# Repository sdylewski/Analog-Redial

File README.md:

# firmware branch

Generated by `firmware/release/release.py`: the images and `latest.json` that a board's web page reads for "Check for updates". Force-pushed on every release; it only ever holds the current one. Don't edit by hand.

Current release: **v1.3.8** (2026-11-25).

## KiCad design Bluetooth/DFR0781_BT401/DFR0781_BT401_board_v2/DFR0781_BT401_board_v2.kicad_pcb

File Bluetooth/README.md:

# Bluetooth modules for the J2 header

What has been tried for the hands-free "rotary phone as a cell-phone handset" option. Newest information first.

| Module | Price | Status |
|---|---|---|
| **DFRobot DFR0781** (BT401 module, `DFR0781_BT401/`) | about $3.50 | **Preferred, and working** (hand-wired to a v5 board 2026-10-27, then on the adapter board): pairing, music, ringing, dial-out and call audio, with little call delay. Text command set with call control (answer, hang up, reject, dial, caller number); no EEPROM setup step. Adapter board `DFR0781_BT401/DFR0781_BT401_board_v1/` plugs into J2 like the BM64 carrier (built, 2026-11-19; Gerbers via KiCad's JLCPCB/PCBWay export); a v2 is in `DFR0781_BT401_board_v2/`. Build guide: [`docs/bt401.md`](../docs/bt401.md). Pin table in `DFR0781_BT401/BT401_NOTES.md`, firmware and bench log in `../archive/hardware/bt401.md`. |
| **Microchip BM64** (carrier board in `BM64/`) | about $14 | **Works and is supported**, the older alternative. UART link, pairing mode and the audio EEPROM setup verified (2026-10-20). Supply 3.2-4.2 V on `BAT_IN`, so it needs the LDO. Costs more and needs a one-time EEPROM setup that the BT401 doesn't. |
| Microchip BM83 | about $12.20 | Candidate only. Digikey lists BM83SM1-00AA, -00AB and -00TA (read the Microchip ordering table before buying). Same 0xAA binary framing as the BM64 per Microchip's UART command documentation, so the driver would probably adapt, but footprint and pinout are not confirmed to match; needs its own carrier. Not worth the $1.80 saving unless the BM64 becomes hard to get. |
| **BK3266 / "BH519"** (`BK3266_do_not_use/`, `BK3266_board_v1` KiCad project) | about $3 | **Not working as intended.** The module powers on and pairs with a phone as an audio device ("BH519"), but its UART never answers (binary or text, 1200-460800 baud, TX/RX both ways), so the firmware cannot control calls. Notes and bench log: `BK3266_do_not_use/BK3266_RESEARCH.md` and `../archive/hardware/bk3266.md`. Kept for reference only; its firmware driver was removed (last in `v1.0.1`). |

Firmware lives in `firmware/components/bt_companion/` (the BM64 and BT401 drivers). The public docs lead with the BT401 ([`docs/bt401.md`](../docs/bt401.md), [`docs/bom.md`](../docs/bom.md#bluetooth-board-v5-and-v6-expansion-header-optional)) and describe the BM64 as the alternative.

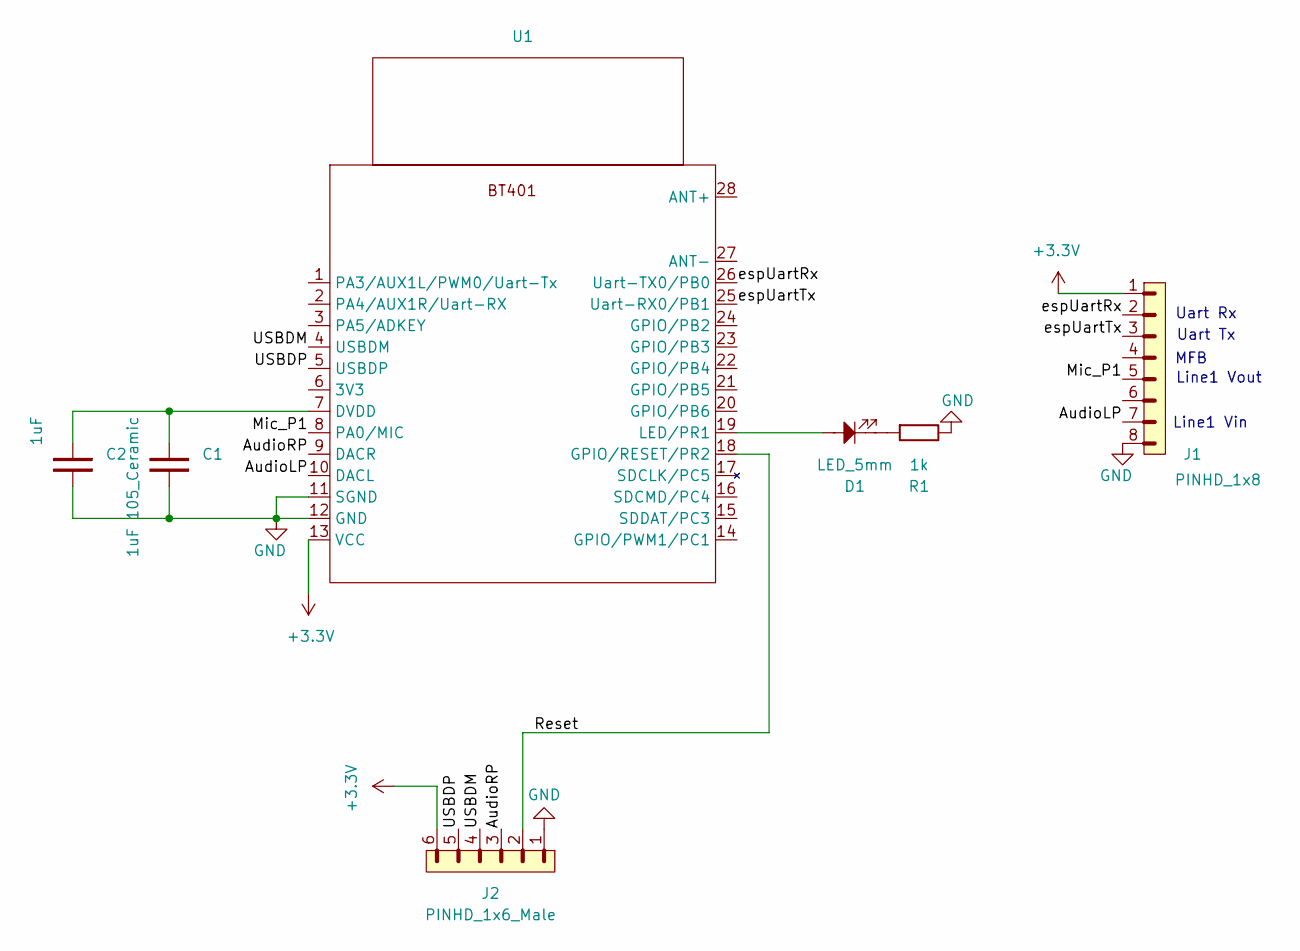
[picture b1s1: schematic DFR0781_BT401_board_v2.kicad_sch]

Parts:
C1: 1uF 105_Ceramic; C_Disc_D5.0mm_W2.5mm_P5.00mm
C2: 1uF; C_0402_1005Metric
D1: LED_5mm; LED_D5.0mm
J1: PINHD_1x8; PinHeader_1x08_P2.54mm_Vertical
J2: PINHD_1x6_Male; PinHeader_1x06_P2.54mm_Vertical
R1: 1k; R_Axial_DIN0207_L6.3mm_D2.5mm_P10.16mm_Horizontal
U1: DFR0781_BT401_new

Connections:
+3.3V: J1.1, J2.6, U1.13 (VCC)
/AudioLP: J1.7, U1.10 (DACL)
/AudioRP: J2.3, U1.9 (DACR)
/Mic_P1: J1.5, U1.8 (PA0/MIC)
/Reset: J2.2, U1.18 (GPIO/RESET/PR2)
/USBDM: J2.4, U1.4 (USBDM)
/USBDP: J2.5, U1.5 (USBDP)
/espUartRx: J1.2, U1.26 (Uart-TX0/PB0)
/espUartTx: J1.3, U1.25 (Uart-RX0/PB1)
GND: C1.2, C2.2, J1.8, J2.1, R1.2, U1.11 (SGND), U1.12 (GND)
unnamed: D1.1, R1.1
unnamed: C1.1, C2.1, U1.7 (DVDD)
unnamed: D1.2, U1.19 (LED/PR1)

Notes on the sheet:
Uart Tx
Line1 Vin
Uart Rx
Line1 Vout
MFB

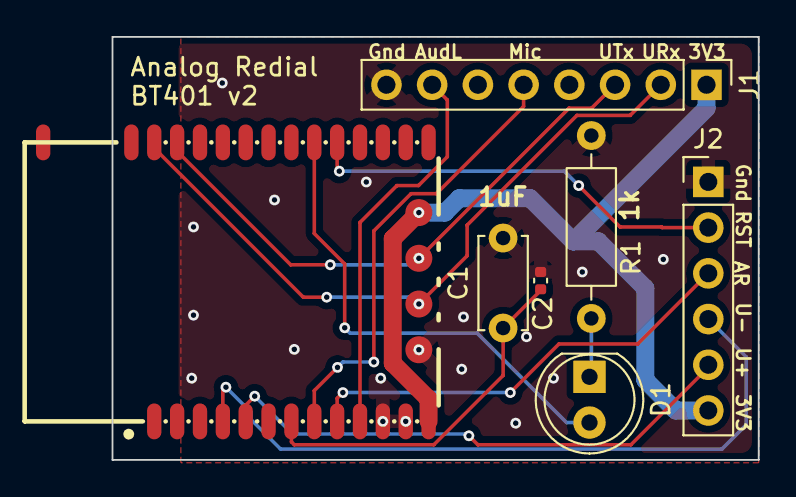
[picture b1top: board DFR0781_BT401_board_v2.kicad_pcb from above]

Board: 2 copper layers, 35.9 x 23.5 mm, 7 parts (0 on the bottom side), 13 nets.

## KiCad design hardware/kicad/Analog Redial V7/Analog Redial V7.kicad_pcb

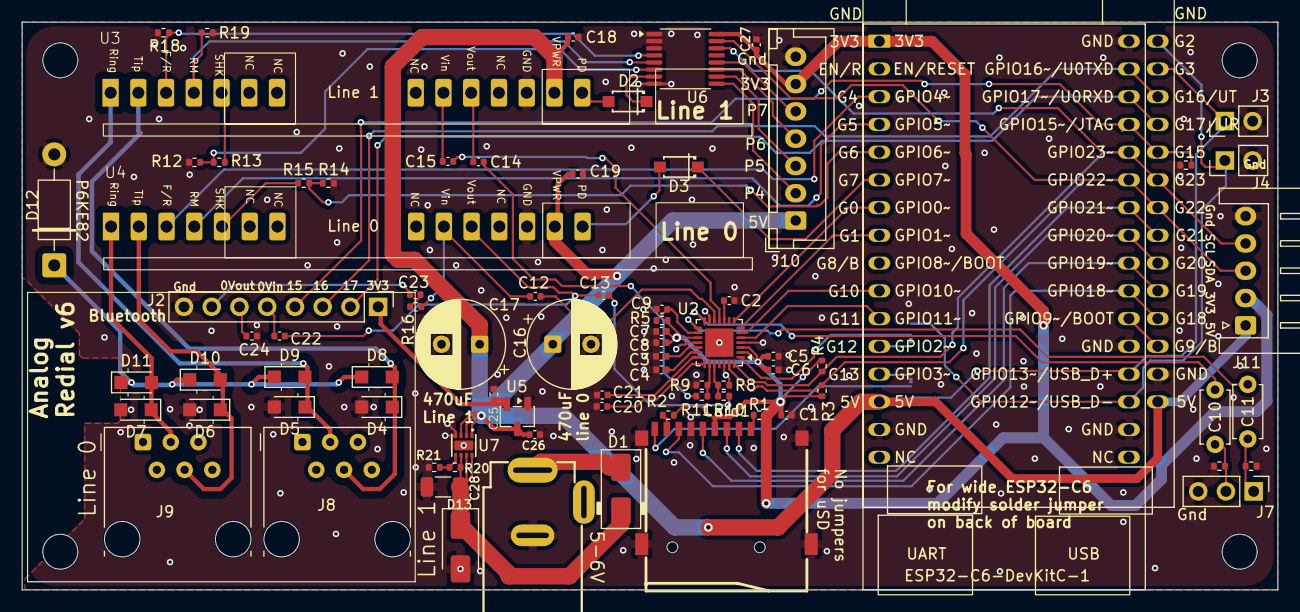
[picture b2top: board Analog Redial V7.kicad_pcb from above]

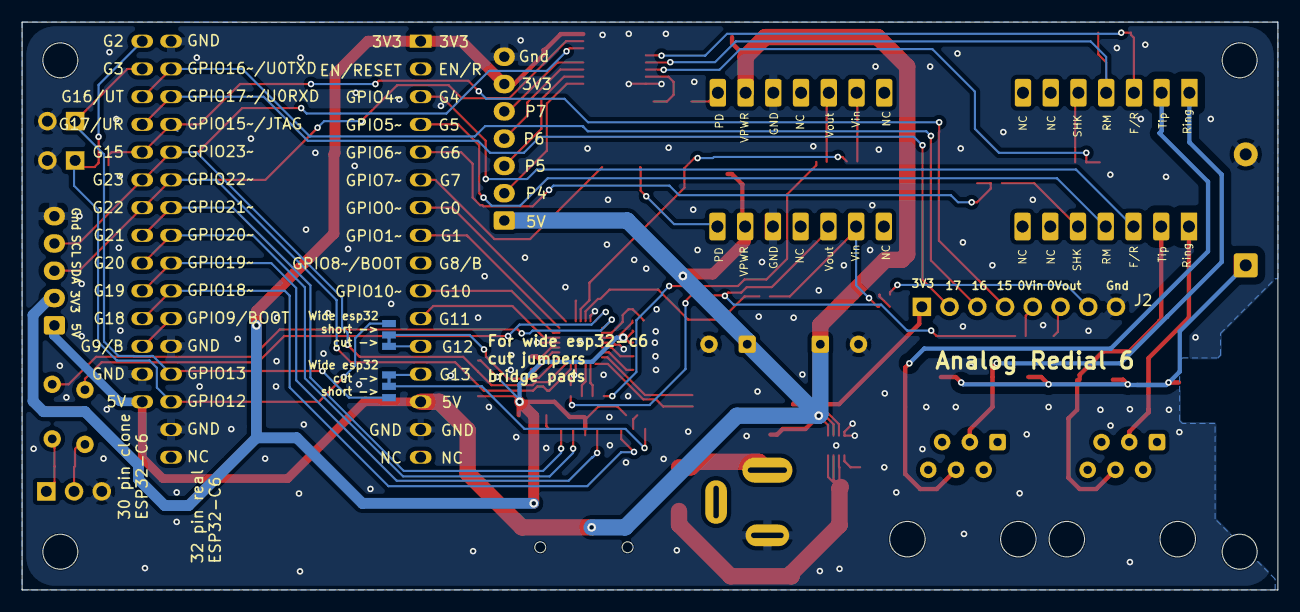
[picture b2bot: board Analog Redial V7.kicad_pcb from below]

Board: 2 copper layers, 115.0 x 52.0 mm, 85 parts (2 on the bottom side), 73 nets.

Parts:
C1, C5, C6, C8, C9, C13, C14, C18, C19, C20, C21, C27: 100nF; C_0402_1005Metric
C2, C3, C4, C22, C23, C24, C25, C26: 1uF; C_0402_1005Metric
C7: 10uF; C_0402_1005Metric
C10, C11: 47uF; C_Disc_D4.7mm_W2.5mm_P5.00mm
C12, C15: 10nF; C_0402_1005Metric
C16, C17: 470uF 16V; CP_Radial_D8.0mm_P3.50mm
C28: 1uF 50V; C_1206_3216Metric
Card1: TF-01A
D1: SS34; D_SMA
D2, D3: 1N4148; 1N4148W_C81598
D4, D5, D6, D7, D8, D9, D10, D11: SM4007PL; Nexperia_CFP3_SOD-123W
D12: D_Zener P6KE82; D_DO-41_SOD81_P10.16mm_Horizontal
D13: SMAJ22A; D_SMA
H1, H2, H3, H4: MountingHole_M3; MountingHole_3.2mm_M3
J1: Barrel_Jack_PTH_Slot; Barrel_Jack_PTH_Slot_tight
J2: PINHD_1x8_Male; PinHeader_1x08_P2.54mm_Vertical
J3, J4: PINHD_1x2_Male; PinHeader_1x02_P2.54mm_Vertical
J7: PINHD_1x3_Male; PinHeader_1x03_P2.54mm_Vertical
J8, J9: RJ12; RJ12_Amphenol_87180_Horizontal
J10: GPIO Expansion; JST_XH_B7B-XH-A_1x07_P2.50mm_Vertical
J11: Accessory; JST_XH_S5B-XH-A_1x05_P2.50mm_Horizontal
JP2, JP3: Jumper_3_NC-1_Trace_NoSilk
R1, R2, R8, R9, R10, R11, R13, R15, R18, R19, R21: 10k; R_0402_1005Metric
R3, R4: 4.7k; R_0402_1005Metric
R5: 10R; R_0402_1005Metric
R6, R7: 47k; R_0402_1005Metric
R12, R14, R17: 100k; R_0402_1005Metric
R16: 1k; R_0402_1005Metric
R20: 39k; R_0402_1005Metric
U1: ESP32-C6-DevKitC-1; ESP32-C6-DevKitC-dual
U2: ES8388; QFN-28-1EP_4x4mm_P0.45mm_EP2.6x2.6mm
U3, U4: AG1171; AG1171_SIL
U5: XC6206P332MR; SOT-23-3
U6: TCA9534APWR; TSSOP-16_4.4x5mm_P0.65mm
U7: WS3222D-8/TR; WS3222D_WDFN-8_2x2mm_P0.5mm

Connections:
+3.3V: C1.1, C5.2, C6.2, C7.2, C8.2, C27.1, Card1.4 (VDD), J10.6, J11.2, R1.2, R2.1, R3.1, R4.1, R5.1, U1.1 (3V3), U2.2 (DVDD), U2.3 (PVDD), U2.17 (AVDD), U6.16 (VDD)
+3.6V_BM: C25.1, J2.1, U5.2 (VO)
+5V: C16.1, C17.1, C18.1, C19.1, C26.1, J10.1, J11.1, U1.14 (5V), U3.13 (Vpwr), U4.13 (Vpwr), U5.3 (VI), U7.1 (OUT), U7.2 (OUT), U7.3 (OUT)
/CH0_Mic: C13.1, R10.1
/CH0_Spk: C12.1, U2.12 (LOUT1)
/CH1_Mic: C14.2, R11.1
/CH1_Spk: C15.2, U2.11 (ROUT1)
/EXP_P4: J10.2, U6.9 (P4)
/EXP_P5: J10.3, U6.10 (P5)
/EXP_P6: J10.4, U6.11 (P6)
/EXP_P7: J10.5, U6.12 (P7)
/GPIO12: J4.1, JP3.3 (B), U1.19 (GPIO12/USB_D-)
/GPIO13: J3.1, JP2.3 (B), U1.20 (GPIO13/USB_D+)
/I2C_SCL: J11.4, R4.2, U1.28 (GPIO23), U2.28 (CCLK), U6.14 (SCL)
/I2C_SDA: J11.3, R3.2, U1.27 (GPIO22), U2.27 (CDATA), U6.15 (SDA)
/I2S_BCLK: U1.11 (GPIO11), U2.5 (SCLK)
/I2S_DIN: U1.7 (GPIO0), U2.8 (ASDOUT)
/I2S_DOUT: U1.10 (GPIO10), U2.6 (DSDIN)
/I2S_LRCK: U1.8 (GPIO1), U2.7 (LRCK)
/I2S_MCLK: JP3.2 (C), U2.1 (MCLK)
/Line0Vin: C12.2, R16.1, U4.9 (Vin)
/Line0Vout: C13.2, C22.1, U4.10 (Vout)
/Line0_F/R: U1.3 (GPIO4/MTMS), U4.3 (F/R)
/Line0_PD: D3.1 (K), U1.6 (GPIO7)
/Line0_RM: U1.4 (GPIO5/MTDI), U4.4 (RM)
/Line0_SHK: R14.2, R15.1, U1.5 (GPIO6)
/Line1Ring: D7.1 (K), D11.2 (A), J9.3, U4.1 (Ring)
/Line1Tip: D6.1 (K), D10.2 (A), J9.4, U4.2 (Tip)
/Line1_F/R: R18.2, U3.3 (F/R), U6.4 (P0)
/Line1_PD: D2.1 (K), U6.7 (P3)
/Line1_RM: R19.2, U3.4 (RM), U6.5 (P1)
/Line1_SHK: R12.2, R13.1, U6.6 (P2)
/Line2Ring: D5.1 (K), D9.2 (A), J8.3, U3.1 (Ring)
/Line2Tip: D4.1 (K), D8.2 (A), J8.4, U3.2 (Tip)
/MFB: J2.4, R17.2, U1.29 (GPIO15/JTAG)
/P6K: D8.1 (K), D9.1 (K), D10.1 (K), D11.1 (K), D12.1 (K)
/SD_CD: Card1.9 (CD), JP2.2 (C)
/SD_CLK: Card1.5 (CLK(SCLK)), U1.24 (GPIO19)
/SD_CS: Card1.2 (CDDAT3(CS)), U1.26 (GPIO21)
/SD_MISO: Card1.7 (DAT0(D0)), U1.23 (GPIO18)
/SD_MOSI: Card1.3 (CMD(DI)), U1.25 (GPIO20)
/VDC_IN: C28.1, D1.1 (K), D13.1 (K), R20.1, U7.6 (IN), U7.7 (IN), U7.8 (IN)
GND: C1.2, C2.1, C3.1, C4.1, C5.1, C6.1, C7.1, C8.1, C9.1, C16.2, C17.2, C18.2, C19.2, C20.1, C21.1, C24.1, C25.2, C26.2, C27.2, C28.2, Card1.6 (VSS), Card1.10 (GND), Card1.11 (GND), Card1.12 (GND), Card1.13 (GND), D4.2 (A), D5.2 (A), D6.2 (A), D7.2 (A), D12.2 (A), D13.2 (A), J1.GND, J2.8, J3.2, J4.2, J7.3, J10.7, J11.5, R6.1, R7.2, R8.1, R9.1, R12.1, R14.1, R17.1, R18.1, R19.1, R21.2, U1.15 (GND), U1.18 (GND), U1.21 (GND), U1.32 (GND), U2.4 (DGND), U2.13 (HPGND), U2.18 (AGND), U2.26 (CE), U2.29 (EPAD), U3.12 (GND), U4.12 (GND), U5.1 (GND), U6.1 (A0), U6.2 (A1), U6.3 (A2), U6.8 (GND), U7.4 (GND), U7.9 (GND)
unnamed: C10.1, J7.2, R6.2
unnamed: C11.1, J7.1, R7.1
unnamed: C22.2, J2.5
unnamed: C23.1, R16.2
unnamed: C23.2, J2.7
unnamed: C24.2, J2.6
unnamed: Card1.8 (DAT1(RSV)), R2.2
unnamed: Card1.1 (DAT2(RSV)), R1.1
unnamed: D1.2 (A), J1.PWR
unnamed: D2.2 (A), U3.14 (PD)
unnamed: D3.2 (A), U4.14 (PD)
unnamed: JP2.1 (A), U1.13 (GPIO3)
unnamed: JP3.1 (A), U1.12 (GPIO2)
unnamed: J2.3, U1.31 (GPIO16/U0TXD)
unnamed: J2.2, U1.30 (GPIO17/U0RXD)
unnamed: C3.2, U2.19 (ADCVREF)
unnamed: C9.2, R5.2, U2.16 (HPVDD)
unnamed: R8.2, R10.2, U2.24 (LIN1)
unnamed: C20.2, U2.22 (LIN2)
unnamed: C11.2, U2.15 (LOUT2)
unnamed: R9.2, R11.2, U2.23 (RIN1)
unnamed: C21.2, U2.21 (RIN2)
unnamed: C10.2, U2.14 (ROUT2)
unnamed: C4.2, U2.20 (VMID)
unnamed: C2.2, U2.10 (VREF)
unnamed: R13.2, U3.5 (SHK)
unnamed: C15.1, U3.9 (Vin)
unnamed: C14.1, U3.10 (Vout)
unnamed: R15.2, U4.5 (SHK)
unnamed: R20.2, R21.1, U7.5 (OVLO)

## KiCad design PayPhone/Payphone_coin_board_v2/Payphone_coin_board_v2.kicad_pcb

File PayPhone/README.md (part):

# Payphone with Analog Redial

**Working on one payphone.** One coin board v1 is built, on a v6 main board, and runs the
project's first phone, a GTE / Quadrum 120B style set: coins are counted from its coin
switches, a message plays for each, and the coins are collected or returned by its coin relay
(2026-11-14 and 15). No other phone has been tried. Coin board v2 (an on-board 3.3 V regulator
and a ground-start relay on P7) is being drawn in `Payphone_coin_board_v2/`.

> ⚠️ **The coin board makes up to 119 V DC and stores it in a capacitor: it can injure or
> kill.** Read [Safety first](../docs/hardware-coin-board.md#safety-first-high-voltage) before
> you build or power one. It is provided as is.

Analog Redial can run a real coin payphone: the handset lifts, a spoken message asks for
coins, the coin switches (or the line's coin tones) add up the credit, and the board
collects or returns the coins by firing the phone's coin relay.

| Doc | Covers |
|---|---|
| This one | the project as a whole: what the pieces are, status, payphone types, links |
| [docs/coin-board.md](docs/coin-board.md) | the coin board: how it works, output stage wiring pin by pin, parts and PCB layout |
| [docs/payphone-firmware.md](docs/payphone-firmware.md) | the firmware: the Payphone tab (coin tones, coin required, messages, log) and the coin board's driver |

Public version of the board reference: [docs/hardware-coin-board.md](../docs/hardware-coin-board.md).

## The pieces

- **Main board:** any Analog Redial board for the Payphone tab (coin required, messages,
  coin tones, the coin counter). The coin board plugs into v6's J11 I²C header.
- **Coin board** (`Payphone_coin_board_v1/`): makes up to 119 V to fire the coin relay in
  either direction, reads the 5 / 10 / 25 cent switches, and talks I²C. One built and working.
- **Instruction cards** (`instruction_cards/`): the printed cards for the phone's
  upper and lower panels, and their standard sizes (see its README).
- **Firmware** (`firmware/components/payphone/`, `coinboard/`): see
  [docs/payphone-firmware.md](docs/payphone-firmware.md).

*Coin board v1 mounted in the phone on a 3D-printed bracket (`Payphone_coin_board_v2/Coin board bracket/`).*

*Coin board v1 mounted in the phone on a 3D-printed bracket (`Payphone_coin_board_v2/Coin board bracket/`).*

## Payphone types

Payphones differ in how they report coins and how their coin relay is driven. The housing
says little: a Quadrum is only a case, and the same case held many different boards. What
matters is **what handles the coins**, and the Payphone tab's **Phone type** card asks for
both, in that order (`firmware/components/payphone/payphone_types.c`, see
[docs/payphone-firmware.md](docs/payphone-firmware.md#phone-type)).

**What handles the coins** (the categories the firmware uses):

| Inside | Coins seen by | Relay worked by | Analog Redial's part |
|---|---|---|---|
| **Coin switches and relay wired to the coin board** (own board removed or bypassed) | the coin board | the coin board, 19-119 V | everything: credit, messages, collect and return |
| **Smart (COCOT) board, working and programmed**: Elcotel, Protel, Intellicall, Ernest, AT&T Private Payphone, Nortel Millennium | the phone's board | the phone's board | only the line; untried. Most need programming with their own software and a modem; an Elcotel 5 also needs a 6 V battery and line voltage for its escrow relay |
| **Coin-line totalizer** (the telephone companies' "dumb" phones: WE 1C, 1D, 2C, Gemini 4032C) | coin tones on the line (1700 + 2200 Hz) | on a real coin line, the exchange, with about ±130 V on the line; here, the coin board if the relay's wires are moved to J2 (untried) | credit and messages from the tones. A coin-first board also waits for a ground start (coin board v2) |
| **No coin board: used as a phone** (the phone's own coin parts left alone) | coin tones on the line, if the phone sends any (untried) | nobody: coins can't be collected or returned | dial tone, ringing and calls; optionally credit and messages from the tones |
| **Coinless** | - | - | nothing: a normal phone |

**Housings** in the menu, with the insides each is found with (usual first):

| Housing | Made | Insides |
|---|---|---|
| Quadrum / GTE 120B style (smart-phone housings; they differ in where the coin return lever is) | 1980s-2000s | coin board, no coin board, smart, coinless |
| Western Electric / AT&T single-slot (1C, 1D, 2C) | 1965-1990s | coin-line, no coin board, smart (retrofits: Protel 4000/8000, Elcotel 5501), coin board, coinless |
| Western Electric 3-slot (coins ring bells and a gong, no tones) | 1920s-1960s | coinless |
| Nortel Millennium | 1990s-2000s | smart, no coin board, coinless |
| Other, or not sure | | any; "not sure" sets nothing and shows every card |

Single-slot board names (from telesfor.org): first digit 1 wall, 2 flush, 3 electronic; letter
A coin first, C coin first or dial tone first, D dial tone first, E postpay; last digit 1 rotary,
2 Touch-Tone, 3 manual. So a 1D2 is a wall-mounted, dial-tone-first, Touch-Tone phone.

Only the coin board choice, on the first phone, has been tried. The menu labels every other
choice "untested" until a phone has been shown to work with it, and the Coin tones card carries
the same label: no real phone's coin tones have been heard yet.

The tables below are what has been **measured**, one row per phone. A measured phone is also a
`KNOWN[]` entry in `payphone_types.c`, so choosing it fills in the coin board's pulse and swap (when the entry has a swap).

To add a phone, add a row to each table (and a `KNOWN[]` entry), mark anything not measured
**[verify]**, and note in the last column where the numbers came from.

### 1. Identification

| Phone | Housing | Controller board | Made | Source |
|---|---|---|---|---|
| **GTE / Quadrum 120B style** (the project's first phone) | GTE / Quadrum, coin return lower right | **HB-1301-B** (40-pin DIP, two CP Clare reed relays, 310 V gas tube); smart or dumb not known **[verify]** | week 51, 1997 | photos and bench tests, 2026-10-24 to 2026-10-31 |

### 2. Coin detection

| Phone | Sensor | Cable | Wires | Signal | Coins | Coin tones |
|---|---|---|---|---|---|---|
| GTE / Quadrum 120B style | passive coin switches (measured) | 4-wire, Molex KK 396 (coin board J3) | green common; white quarter, red dime, blue nickel | contact to common; closes for 40-95 ms per coin (measured with the coin switch capture: nickel 44-95 ms, dime 44-51 ms, quarter about 40 ms, with up to 3 ms of chatter at first contact) | 5, 10, 25 cents | not checked **[verify]** |

### 3. Coin relay

| Phone | Relay | Coils | Wires | Resistance | Operates at | Direction | Switch-off | Cable |
|---|---|---|---|---|---|---|---|---|
| GTE / Quadrum 120B style | **HD550002C** (QTI) | one, polarized | white and green to the coil path; red not connected | about 1 k at rest; 0.1 ohm across the coil once operated | 55 V no, 60 V yes on the bench (relay alone); **in the phone it needs 87 V** (about 67 mA through the 1.1 k coil) | white positive: lever left, **collect** (bench; confirm in the phone) **[verify]**; reversed: lever right, return | a contact on the white-green path opens as it operates, so it switches itself off | 3-wire, Molex KK 396 (coin board J2) |

### 4. Coin board settings

| Phone | Relay connector | J10 (two-coil) | HV (J14, J7-J9) | Pulse | Swap | Coin 4 | Tested |
|---|---|---|---|---|---|---|---|
| GTE / Quadrum 120B style | J2 | off | fit **J14 + J7 (87 V)**; 60 V and 78 V don't give the relay enough current with the phone's levers attached | 100 ms works (the armature moves at about 65-70 ms, seen as a dip in the coil current); 100-150 ms | **off** (the default): confirmed in the phone, collect and return both go the right way. On the bench alone, white positive collected, which looked like "on" | 0 (not fitted) | **yes**: collect and return in the phone, on answer and at hang-up (2026-11-14/15, 87 V, 100 ms) |

Notes on the columns:

- **HV** is set by shunts, not by firmware: [docs/coin-board.md](docs/coin-board.md#part-1-design)
  Part 1, section 6 has the table. Without J14 it stays at about 19 V, for 12-24 V coils.
- **Pulse** and **Swap** are on the Payphone tab's coin board card. Swap reverses which
  way Collect and Return drive the relay.
- **Coin 4** is the cents value of the fourth coin input (0 = only logged).

### What the first phone taught

- **The relay latches its flap down.** After a fire the white flap stays down, and the relay
  can't fire again while it is (its own contact is open): the firmware reports "no current
  (latched down?)". The next coin entering the chute pushes it back up. A stiff coin lever that
  wouldn't return caused the stuck-down states on the bench, and sent every coin straight to
  the box: it needed taking out and oiling.
- **Bench voltage isn't phone voltage.** The relay moved at 60 V on the bench, alone; in the
  phone, with its levers attached, it needs 87 V.
- **Too many coins jam the hopper** when released together, hence the coin limit (8 by
  default) on the Payphone tab.
- **The coin return lever** ("coin release") only widens the coin path to free a jam; it
  doesn't return the hopper's coins.
- **A reversed J3 plug** counts nickels but not dimes or quarters.
- **Marginal 3.3 V on the cable** (a bad crimp, or a clone module's small regulator) gives
  odd ADC readings and resets; coin board v2 has its own regulator for this.

### Still to find out for the first phone

- Whether the HB-1301-B board is smart (counts coins itself) or dumb (central-office
  controlled), and whether the phone sends coin tones on the line. It is bypassed now, so this
  only matters for someone running the phone on its own board.

## References

- [telesfor.org payphone wiki](https://telesfor.org/payphones/doku.php?id=smart): the best single
  reference found. Smart (COCOT) payphones by maker ([Elcotel](https://telesfor.org/payphones/doku.php?id=smart:elcotel),
  [Protel](https://telesfor.org/payphones/doku.php?id=smart:protel),
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
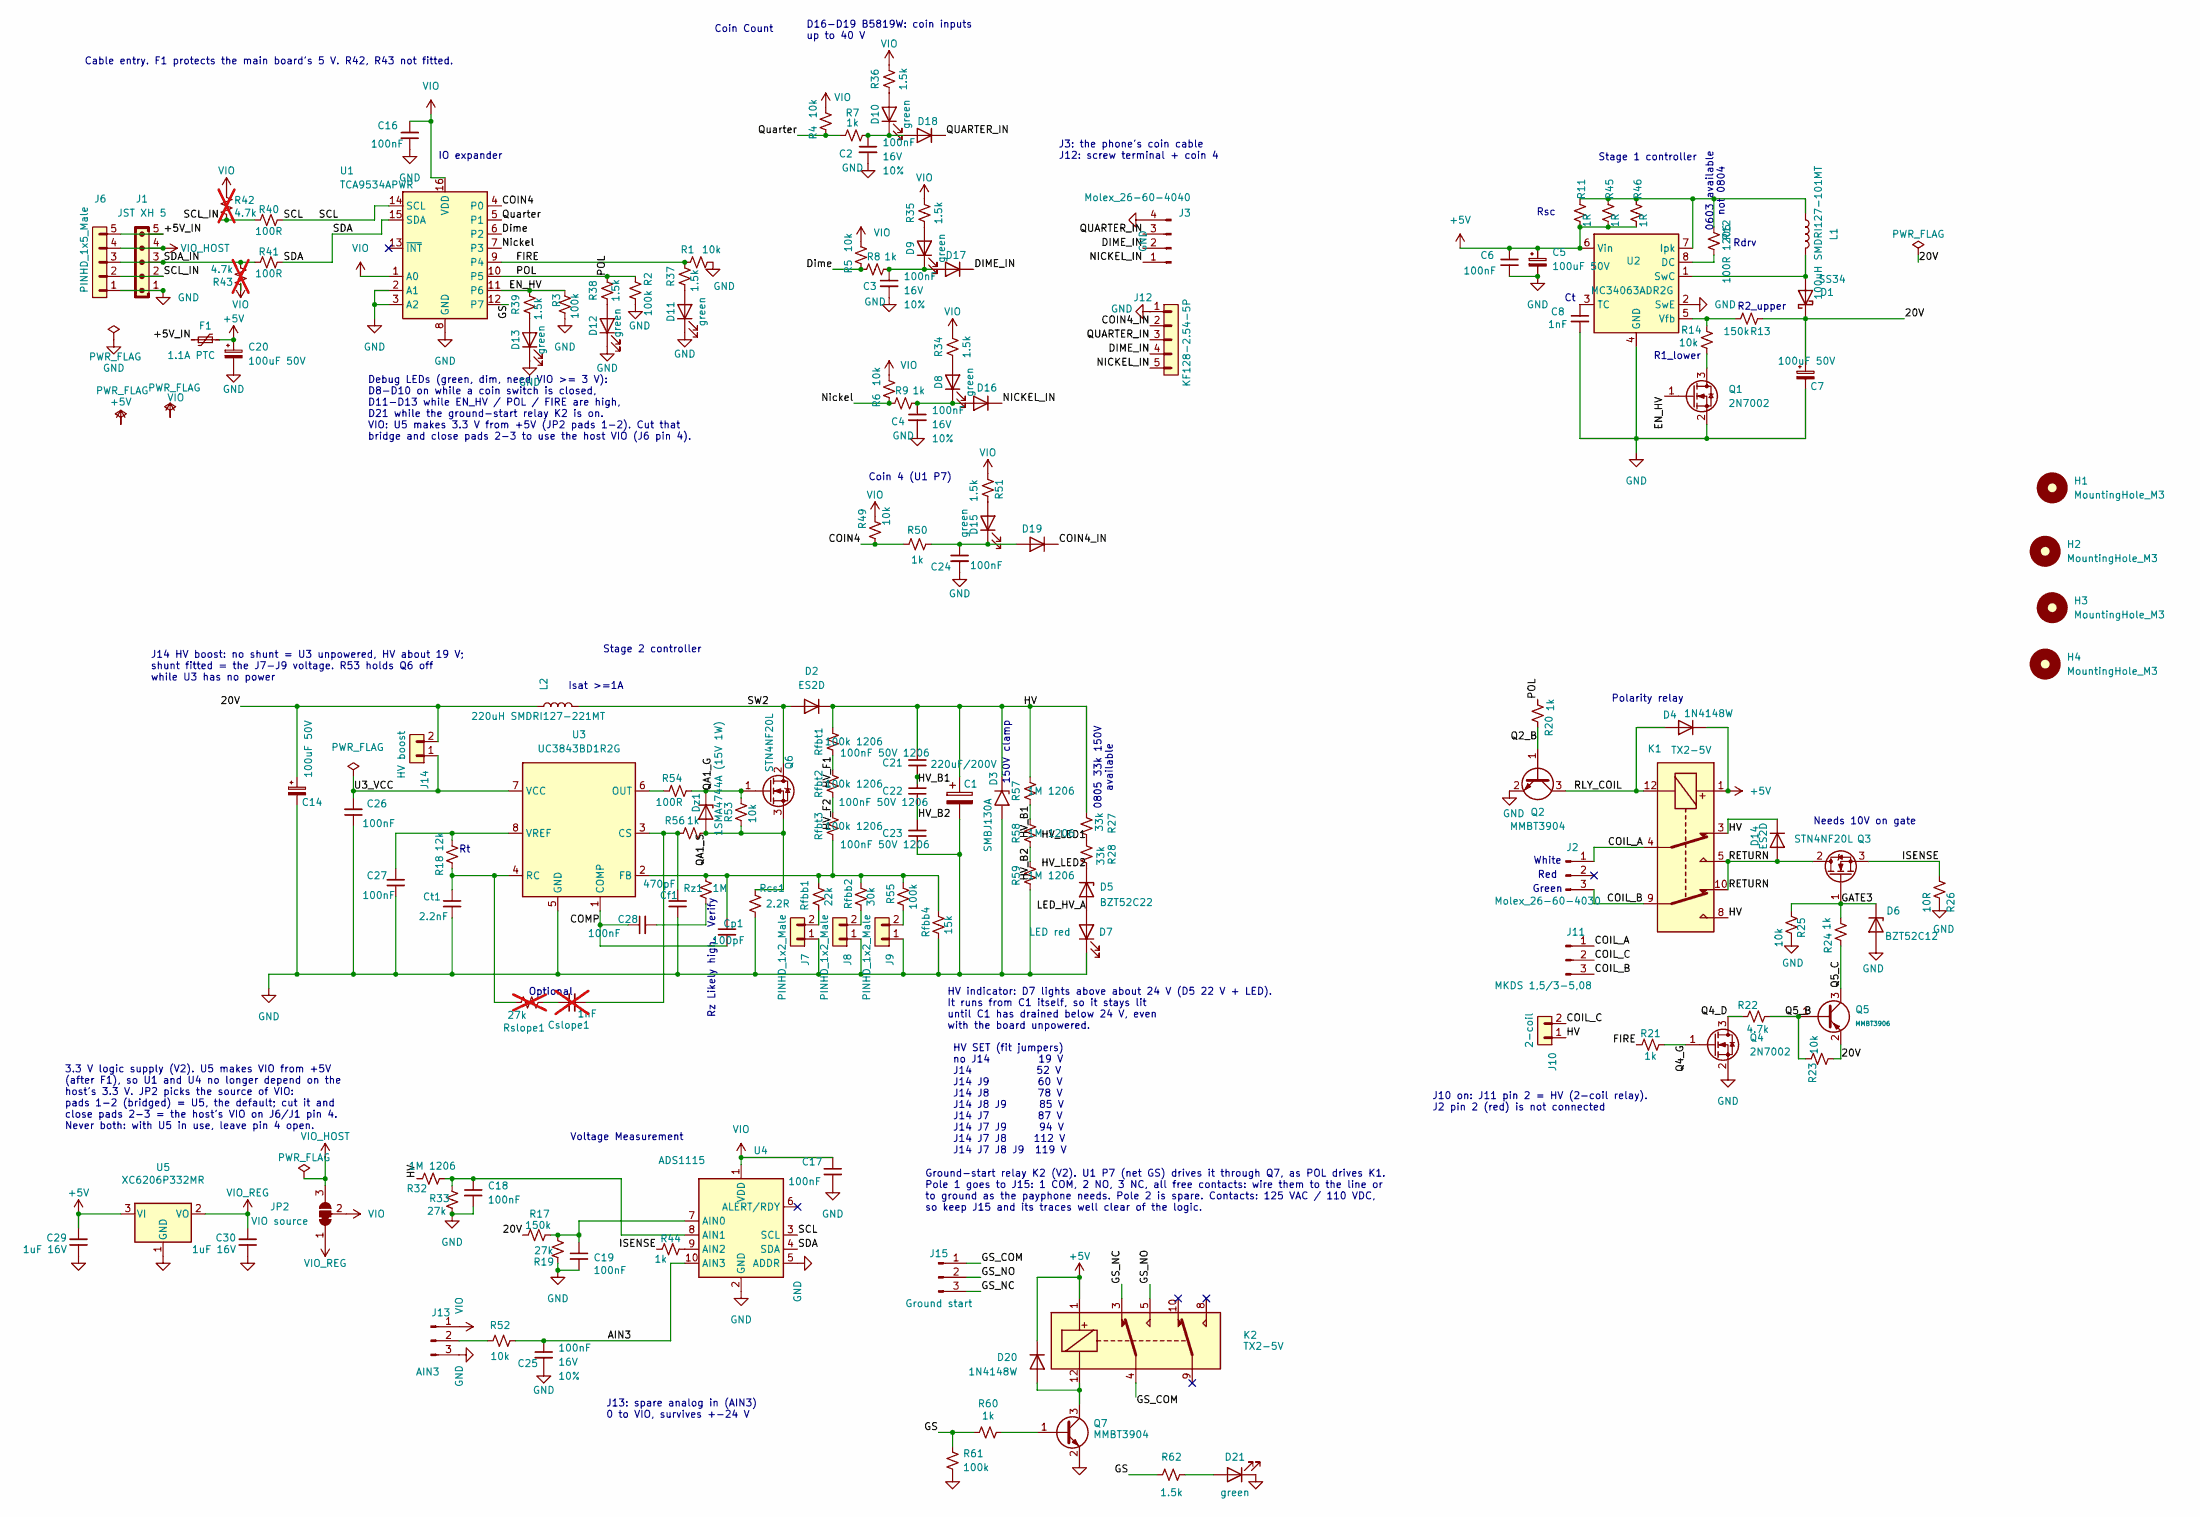
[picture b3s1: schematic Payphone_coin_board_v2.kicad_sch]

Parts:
C1: 220uF/200V; CP_Radial_D18.0mm_P7.50mm
C2, C3, C4, C24, C25: 100nF; C_0805_2012Metric; Voltage 16V; Tolerance 10%; LCSC C28233
C5, C7, C14, C20: 100uF 50V; CP_Elec_8x10
C6, C16, C17, C18, C19, C26, C27, C28: 100nF; C_0805_2012Metric; LCSC C28233
C8: 1nF; C_0805_2012Metric; LCSC C46653
C21, C22, C23: 100nF 50V 1206; C_1206_3216Metric; LCSC C24497
C29, C30: 1uF 16V; C_0805_2012Metric
Cf1: 470pF; C_0805_2012Metric; LCSC C1743
Cp1: 100pF; C_0805_2012Metric; LCSC C1790
Cslope1: 1nF; C_0805_2012Metric; LCSC C46653; not fitted
Ct1: 2.2nF; C_0805_2012Metric; LCSC C28260
D1: SS34; D_SMA; LCSC C8678
D2, D14: ES2D; D_SMA; LCSC C18199161
D3: SMBJ130A; D_SMB
D4, D20: 1N4148W; D_SOD-123; LCSC C81598
D5: BZT52C22; D_SOD-123; LCSC C22375295
D6: BZT52C12; D_SOD-123; LCSC C19077410
D7: LED red; LED_0805_2012Metric; LCSC C84256
D8, D9, D10, D11, D12, D13, D15, D21: green; LED_0805_2012Metric; LCSC C2297
D16, D17, D18, D19: B5819W; D_SOD-123; LCSC C8598
Dz1: 1SMA4744A (15V 1W); D_SMA; LCSC C19077482
F1: 1.1A PTC; Fuse_1812_4532Metric
H1, H2, H3, H4: MountingHole_M3; MountingHole_3.2mm_M3
J1: JST XH 5; JST_XH_B5B-XH-A_1x05_P2.50mm_Vertical
J2: Molex_26-60-4030; Molex_KK-396_A-41791-0003_1x03_P3.96mm_Vertical; MPN 0026604030; DigiKey WM4621-ND
J3: Molex_26-60-4040; Molex_KK-396_A-41791-0004_1x04_P3.96mm_Vertical; MPN 0026604040; DigiKey WM4622-ND
J6: PINHD_1x5_Male; PinHeader_1x05_P2.54mm_Vertical
J7, J8, J9: PINHD_1x2_Male; PinHeader_1x02_P2.54mm_Vertical
J10: 2-coil; PinHeader_1x02_P2.54mm_Vertical
J11: MKDS 1,5/3-5,08; TerminalBlock_Phoenix_MKDS-1,5-3-5.08_1x03_P5.08mm_Horizont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
J12: KF128-2.54-5P; TerminalBlock_Xinya_XY308-2.54-5P_1x05_P2.54mm_Horizontal
J13: AIN3; PinHeader_1x03_P2.54mm_Vertical
J14: HV boost; PinHeader_1x02_P2.54mm_Vertical
J15: Ground start; TerminalBlock_Phoenix_MKDS-1,5-3-5.08_1x03_P5.08mm_Horizont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
JP2: VIO source; SolderJumper-3_P1.3mm_Bridged12_RoundedPad1.0x1.5mm
K1, K2: TX2-5V; Relay_DPDT_Omron_G6S-2
L1: 100uH SMDRI127-101MT; L_SXN_SMDRI127; LCSC C10150
L2: 220uH SMDRI127-221MT; L_SXN_SMDRI127; LCSC C10151
Q1, Q4: 2N7002; SOT-23; LCSC C8545
Q2, Q7: MMBT3904; SOT-23; LCSC C20526
Q3, Q6: STN4NF20L; SOT-223-3_TabPin2; LCSC C7603336
Q5: MMBT3906; SOT-23; Part MMBT3906; LCSC C7420354
R1, R4, R5, R6, R14, R23, R25, R49, R52, R53: 10k; R_0805_2012Metric; LCSC C17414
R2, R3, R55, R61: 100k; R_0805_2012Metric; LCSC C149504
R7, R8, R9, R20, R21, R24, R44, R50, R56, R60: 1k; R_0805_2012Metric; LCSC C17513
R11, R45, R46: 1R; R_1206_3216Metric; LCSC C17928
R12: 100R 1206; R_1206_3216Metric; LCSC C17901
R13, R17: 150k; R_0805_2012Metric; LCSC C17470
R18: 12k; R_0805_2012Metric; LCSC C17444
R19, R33: 27k; R_0805_2012Metric; LCSC C17593
R22: 4.7k; R_0805_2012Metric; LCSC C17673
R26: 10R; R_1206_3216Metric; LCSC C17903
R27, R28: 33k; R_0805_2012Metric_Pad1.20x1.40mm_HandSolder; LCSC C17633
R32, R57, R58, R59: 1M 1206; R_1206_3216Metric; LCSC C17927
R34, R35, R36, R37, R38, R39, R51, R62: 1.5k; R_0805_2012Metric; LCSC C4310
R40, R41, R54: 100R; R_0805_2012Metric; LCSC C17408
R42, R43: 4.7k; R_0805_2012Metric; LCSC C17673; not fitted
Rcs1: 2.2R; R_0805_2012Metric; LCSC C17521
Rfbb1: 22k; R_0805_2012Metric; LCSC C17560
Rfbb2: 30k; R_0805_2012Metric; LCSC C17621
Rfbb4: 15k; R_0805_2012Metric; LCSC C17475
Rfbt1, Rfbt2, Rfbt3: 100k 1206; R_1206_3216Metric; LCSC C17900
Rslope1: 27k; R_0805_2012Metric; LCSC C17593; not fitted
Rz1: 1M; R_0805_2012Metric; LCSC C17514
U1: TCA9534APWR; TSSOP-16_4.4x5mm_P0.65mm; LCSC C206010
U2: MC34063ADR2G; SOIC-8_3.9x4.9mm_P1.27mm; LCSC C32078
U3: UC3843BD1R2G; SOIC-8_3.9x4.9mm_P1.27mm
U4: ADS1115; ADS1115 Module
U5: XC6206P332MR; SOT-23-3; LCSC C5446

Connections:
+5V: C5.1, C6.2, C20.1, C29.1, D4.1 (K), D20.1 (K), F1.2, K1.1, K2.1, R11.2, R45.2, R46.2, U2.6 (Vin), U5.3 (VI); also elsewhere on the board
/20V: C7.1, C14.1, D1.1 (K), J14.2, L2.1, Q5.2 (E), R13.2, R17.2, R23.1
/+5V_IN: F1.1, J1.5, J6.5
/AIN3: C25.1, R52.1, U4.10 (AIN3)
/COIL_A: J2.1, J11.1, K1.4
/COIL_B: J2.3, J11.3, K1.9
/COIL_C: J10.2, J11.2
/COIN4: R49.1, R50.2, U1.4 (P0)
/COIN4_IN: D19.1 (K), J12.2
/COMP: C28.1, Cp1.1, U3.1 (COMP)
/DIME_IN: D17.1 (K), J3.2, J12.4
/Dime: R5.2, R8.2, U1.6 (P2)
/EN_HV: Q1.1 (G), R3.1, R39.2, U1.11 (P6)
/FIRE: R1.2, R21.1, R37.2, U1.9 (P4)
/GATE3: D6.1 (K), Q3.1 (G), R24.2, R25.1
/HV: C1.1, C21.1, D2.1 (K), D3.1 (A1), D14.1 (K), J10.1, K1.3, K1.8, R27.2, R32.2, R57.2, Rfbt1.2
/HV_B1: C21.2, C22.1, R57.1, R58.2
/HV_B2: C22.2, C23.1, R58.1, R59.2
/HV_F1: Rfbt1.1, Rfbt2.2
/HV_F2: Rfbt2.1, Rfbt3.2
/HV_LED1: R27.1, R28.2
/HV_LED2: D5.1 (K), R28.1
/ISENSE: Q3.3 (S), R26.1, R44.1
/LED_HV_A: D5.2 (A), D7.2 (A)
/NICKEL_IN: D16.1 (K), J3.1, J12.5
/Nickel: R6.2, R9.2, U1.7 (P3)
/POL: R2.2, R20.1, R38.2, U1.10 (P5)
/Q2_B: Q2.1 (B), R20.2
/Q4_D: Q4.3 (D), R22.1
/Q4_G: Q4.1 (G), R21.2
/Q5_B: Q5.1 (B), R22.2, R23.2
/Q5_C: Q5.3 (C), R24.1
/QA1_G: Dz1.1 (K), Q6.1 (G), R53.2, R54.1
/QA1_S: Dz1.2 (A), Q6.3 (S), R53.1, R56.1, Rcs1.2
/QUARTER_IN: D18.1 (K), J3.3, J12.3
/Quarter: R4.2, R7.2, U1.5 (P1)
/RETURN: D14.2 (A), K1.5, K1.10, Q3.2 (D)
/RLY_COIL: D4.2 (A), K1.12, Q2.3 (C)
/SCL: R40.2, U1.14 (SCL), U4.3 (SCL)
/SCL_IN: J1.2, J6.2, R40.1, R42.1
/SDA: R41.2, U1.15 (SDA), U4.4 (SDA)
/SDA_IN: J1.3, J6.3, R41.1, R43.1
/SW2: D2.2 (A), L2.2, Q6.2 (D)
/U3_VCC: C26.2, J14.1, U3.7 (VCC)
GND: C1.2, C2.2, C3.2, C4.2, C5.2, C6.1, C7.2, C8.1, C14.2, C16.2, C17.2, C18.2, C19.2, C20.2, C23.2, C24.2, C25.2, C26.1, C27.1, C29.2, C30.2, Cf1.1, Ct1.1, D3.2 (A2), D6.2 (A), D7.1 (K), D11.1 (K), D12.1 (K), D13.1 (K), D21.1 (K), J1.1, J3.4, J6.1, J7.1, J8.1, J9.1, J12.1, J13.3, Q1.2 (S), Q2.2 (E), Q4.2 (S), Q7.2 (E), R1.1, R2.1, R3.2, R19.1, R25.2, R26.2, R33.1, R59.1, R61.2, Rcs1.1, Rfbb4.1, U1.2 (A1), U1.3 (A2), U1.8 (GND), U2.2 (SwE), U2.4 (GND), U3.5 (GND), U4.2 (GND), U4.5 (ADDR), U5.1 (GND)
unnamed: C28.2, Rz1.1
unnamed: C30.1, JP2.1 (A), U5.2 (VO)
unnamed: Cslope1.2, Rslope1.2
unnamed: D1.2 (A), L1.2, U2.1 (SwC)
unnamed: D8.2 (A), R34.1
unnamed: D9.2 (A), R35.1
unnamed: D10.2 (A), R36.1
unnamed: C2.1, D10.1 (K), D18.2 (A), R7.1
unnamed: D11.2 (A), R37.1
unnamed: D12.2 (A), R38.1
unnamed: D13.2 (A), R39.1
unnamed: D15.2 (A), R51.1
unnamed: C24.1, D15.1 (K), D19.2 (A), R50.1
unnamed: C4.1, D8.1 (K), D16.2 (A), R9.1
unnamed: C3.1, D9.1 (K), D17.2 (A), R8.1
unnamed: D20.2 (A), K2.12, Q7.3 (C)
unnamed: D21.2 (A), R62.2
unnamed: J7.2, Rfbb1.1
unnamed: J8.2, Rfbb2.1
unnamed: J9.2, R55.1
unnamed: J13.2, R52.2
unnamed: J15.1, K2.4
unnamed: J15.2, K2.5
unnamed: J15.3, K2.3
unnamed: Q1.3 (D), R14.2
unnamed: Q7.1 (B), R60.2
unnamed: R60.1, R61.1, R62.1, U1.12 (P7)
unnamed: R12.1, U2.8 (DC)
unnamed: L1.1, R11.1, R12.2, R45.1, R46.1, U2.7 (Ipk)
unnamed: C8.2, U2.3 (TC)
unnamed: R13.1, R14.1, U2.5 (Vfb)
unnamed: Cf1.2, Cslope1.1, R56.2, U3.3 (CS)
unnamed: Cp1.2, R55.2, Rfbb1.2, Rfbb2.2, Rfbb4.2, Rfbt3.1, Rz1.2, U3.2 (FB)
unnamed: R54.2, U3.6 (OUT)
unnamed: Ct1.2, R18.2, Rslope1.1, U3.4 (RC)
unnamed: C27.2, R18.1, U3.8 (VREF)
unnamed: C19.1, R17.1, R19.2, U4.7 (AIN0)
unnamed: C18.1, R32.1, R33.2, U4.8 (AIN1)
unnamed: R44.2, U4.9 (AIN2)

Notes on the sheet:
Voltage Measurement
Rdrv
J14 HV boost: no shunt = U3 unpowered, HV about 19 V; shunt fitted = the J7-J9 voltage. R53 holds Q6 off while U3 has no power
D16-D19 B5819W: coin inputs up to 40 V
R2_upper
Debug LEDs (green, dim, need VIO >= 3 V): D8-D10 on while a coin switch is closed, D11-D13 while EN_HV / POL / FIRE are high, D21 while the ground-start relay K2 is on. VIO: U5 makes 3.3 V from +5V (JP2 pads 1-2). Cut that bridge and close pads 2-3 to use the host VIO (J6 pin 4).
Coin Count
IO expander
Needs 10V on gate
Cable entry. F1 protects the main board's 5 V. R42, R43 not fitted.
0805 33k 150V available
Stage 1 controller
Rz Likely high. Verify
Isat >=1A
Coin 4 (U1 P7)
White
Rsc
Optional
Green
150V clamp
HV SET (fit jumpers) no J14 19 V J14 52 V J14 J9 60 V J14 J8 78 V J14 J8 J9 85 V J14 J7 87 V J14 J7 J9 94 V J14 J7 J8 112 V J14 J7 J8 J9 119 V
HV indicator: D7 lights above about 24 V (D5 22 V + LED). It runs from C1 itself, so it stays lit until C1 has drained below 24 V, even with the board unpowered.
J10 on: J11 pin 2 = HV (2-coil relay). J2 pin 2 (red) is not connected
Red
Polarity relay
0603 available not 0804
R1_lower
Stage 2 controller
J13: spare analog in (AIN3) 0 to VIO, survives +-24 V
J3: the phone's coin cable J12: screw terminal + coin 4
3.3 V logic supply (V2). U5 makes VIO from +5V (after F1), so U1 and U4 no longer depend on the host's 3.3 V. JP2 picks the source of VIO: pads 1-2 (bridged) = U5, the default; cut it and close pads 2-3 = the host's VIO on J6/J1 pin 4. Never both: with U5 in use, leave pin 4 open.
Ground-start relay K2 (V2). U1 P7 (net GS) drives it through Q7, as POL drives K1. Pole 1 goes to J15: 1 COM, 2 NO, 3 NC, all free contacts: wire them to the line or to ground as the payphone needs. Pole 2 is spare. Contacts: 125 VAC / 110 VDC, so keep J15 and its traces well clear of the logic.

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
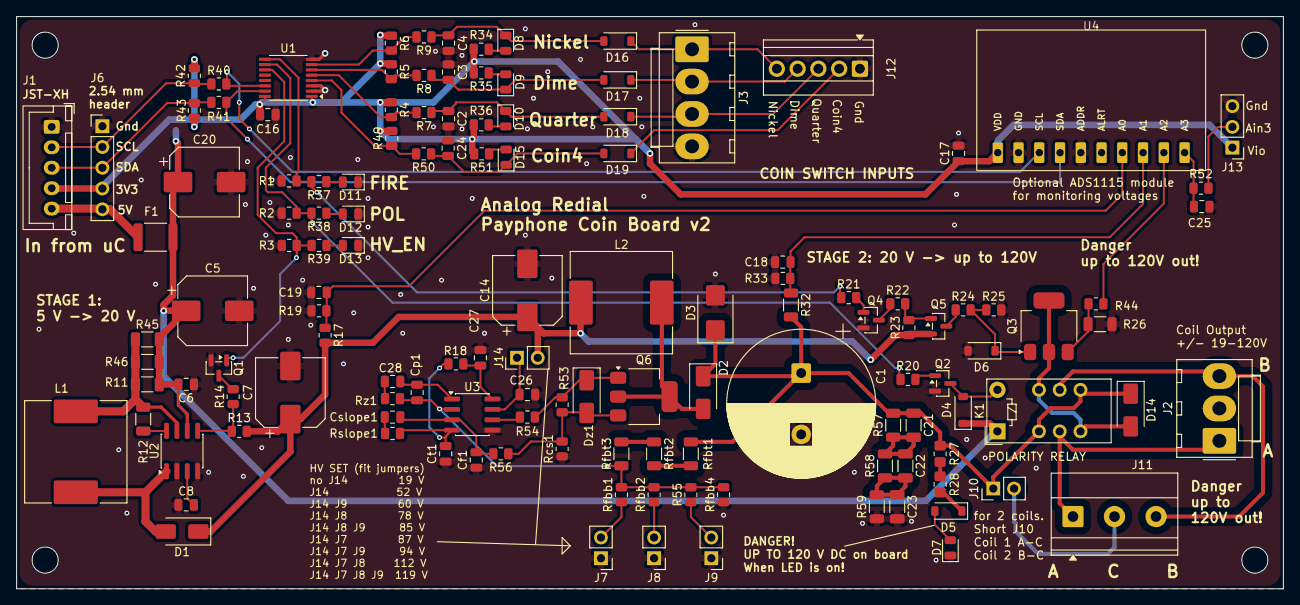
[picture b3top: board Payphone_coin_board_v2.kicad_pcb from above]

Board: 2 copper layers, 155.0 x 70.0 mm, 137 parts (1 on the bottom side), 77 nets.

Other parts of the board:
JP1: VIO=5V; SolderJumper-2_P1.3mm_Open_RoundedPad1.0x1.5mm

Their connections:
+5V: JP1.2 (B); also elsewhere on the board

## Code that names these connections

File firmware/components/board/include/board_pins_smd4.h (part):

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 * ("Pin map (ESP32-C6-DevKitC-1, U1)", confirmed 2026-08-30) and
 * docs/hardware.md section 3. Genuinely different from board_pins_smd.h
 * (SMD2): moving the MCU carrier from a soldered WROOM-1 module to a
 * DevKitC-1 dev board freed up GPIO0/1/2 and remapped I2S there, which in
 * turn pushed line 0's SLIC control onto GPIO4-7 instead of SMD2's I2S
 * pins there. Two specific gotchas worth calling out because they're easy
 * to get backwards from memory or from SMD2's header:
 *
 *   - I2S pins are NOT the same GPIOs as SMD2 (compare BOARD_I2S_* below to
 *     board_pins_smd.h) -- SMD2 put I2S on GPIO0/4/5/6/7; here it's on
 *     GPIO0/1/2/10/11, freeing GPIO4-7 for line 0's SLIC.
 *   - The GPIO18-21 to signal mapping is NOT the same as SMD2's, even
 *     though both boards XOR the same four pins between the shared line's
 *     SLIC and a microSD socket: SMD2 pairs GPIO18 with PD/CS and GPIO21
 *     with F/R and MISO; this board pairs GPIO18 with F/R and MISO, and
 *     GPIO21 with PD and CS -- 18 and 21 are swapped. GPIO19 (SHK/CLK) and
 *     GPIO20 (RM/MOSI) match SMD2. Confirmed against
 *     archive/hardware/smd4.md's J5 jumper table, not carried
 *     over from SMD2's header by assumption.
 *
 * No status LED on this board (GPIO11, SMD2's LED pin, is I2S BCLK here) --
 * BOARD_STATUS_LED is deliberately not defined; board.c's LED code is
 * gated on CONFIG_BOARD_TYPE_SMD2 specifically (not the general "is this
 * an SMD board" check) for exactly this reason, so it correctly no-ops on
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 * "Reference/silk numbering note" if cross-checking against the board
 * itself.
 *
 * Macro naming note: the shared GPIO18-21 group keeps the BOARD_LINE2_PIN_*
 * prefix board.c (board_hw_detect_evidence()) hardcodes by that exact
 * name, even though this board's own documentation calls that same shared
 * line "line 1" -- a naming holdover from SMD2 (where the shared line
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
#if BOARD_LINE1_ON_EXPANDER
/* ---- SMD6: line 1's SLIC (U3) on a TCA9534A (U6, A0-A2 to GND). P4-P7 are the
 * spare pins on J10. GPIO18-21 above are the microSD card's alone. ---- */
#define BOARD_EXP_I2C_ADDR 0x38
#define BOARD_EXP_BIT_FR   0
#define BOARD_EXP_BIT_RM   1
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 * like this one until now, that doesn't define this macro).
 *
 * NOTE: as of the last design-doc update before this board was fabricated,
 * the GPIO3-to-Card1-pin-9 schematic net was still marked "planned, not
 * yet drawn". Confirm this actually reads a real card-detect signal (not
 * floating) during bring-up before trusting it, same as every other pin
 * on a first-fabrication board. */
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#define BOARD_UART_RX     GPIO_NUM_17

/* Bring-up/bench-only: BM64 MFB/RST_N/P2_0 control, for boards that have
 * temporarily wired a BM64 companion module to the same GPIO18-20 pads line
 * 1's SLIC/microSD would otherwise use (see the shared-pad comment above).
 * These #defines exist on every SMD4 board unconditionally (harmless if
 * unused), but the pins themselves are only safe to actually drive when
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 * fixed resistor instead and has no GPIO control over any of these three. */
#if CONFIG_BOARD_TYPE_SMD5 || \
    CONFIG_BOARD_TYPE_SMD6
/* SMD5 gives MFB a pin of its own on the expanded J12 header: GPIO15, the
 * only genuinely spare pin on this pin map (GPIO8 drives the DevKit's RGB
 * LED, GPIO9 is the download-mode strap -- MFB's pull-down there would boot
 * the board into download mode every time). GPIO15 is a strapping pin too,
 * but it only selects the JTAG source and only when an eFuse that ships
 * unburned is set, so an external 100k pull-down on it is harmless.
 * Because it's dedicated, MFB works on a 2-line/microSD board as well --
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#define BOARD_BT_MFB_PIN  GPIO_NUM_15
#define BOARD_BT_MFB_DEDICATED 1
#else
#define BOARD_BT_MFB_PIN  BOARD_LINE2_PIN_FR_MISO  /* GPIO18 */
#endif
#define BOARD_BT_RST_PIN  BOARD_LINE2_PIN_SHK_SCLK /* GPIO19 */
#define BOARD_BT_P20_PIN  BOARD_LINE2_PIN_RM_MOSI  /* GPIO20 */

/* No status LED on this board -- BOARD_STATUS_LED intentionally not
 * defined, see this file's own top-of-file comment. */
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/* Always returns line 1's real pins regardless of runtime config -- this is
 * just the pin map, not a claim that line 1 is actually populated/active.
 * Callers (ag1170's line-1 init) must check board_hw_config_get().num_lines
 * before actually configuring these as a SLIC; on a board where GPIO18-21
 * are wired to a microSD instead, driving them as SLIC control lines would
 * just be wrong, not merely unused. */
static inline board_line_pins_t board_line_pins(int line)
{
    if (line == 0) {
        return (board_line_pins_t){ BOARD_LINE0_SHK, BOARD_LINE0_FR,
                                    BOARD_LINE0_RM,  BOARD_LINE0_PD };
    }
    return (board_line_pins_t){ BOARD_LINE1_SHK, BOARD_LINE1_FR,
                                BOARD_LINE1_RM,  BOARD_LINE1_PD };
}

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
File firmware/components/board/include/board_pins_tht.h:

/*
 * board_pins_tht.h — ESP32-C6 Rotary Phone Gateway pin map.
 *
 * SINGLE SOURCE OF TRUTH for GPIO assignments. Mirrors the routed PCB
 * (hardware/kicad/rotary_phone_gateway) and hardware/WM8731.md.
 *
 * Lines are 0-indexed in firmware:
 *   LINE 0 = "Line 1" on the schematic (SLIC U5, jack J1, codec LEFT  channel)
 *   LINE 1 = "Line 2" on the schematic (SLIC U4, jack J2, codec RIGHT channel)
 *
 * Do NOT use GPIO8, GPIO9, GPIO15 (boot/JTAG straps) or GPIO12/GPIO13 (USB).
 */
#pragma once

#include "driver/gpio.h"
#include "board_config.h"

/* Always 2 -- unlike SMD2, this PCB has no line2/microSD GPIO-sharing
 * tradeoff (dedicated pins for both lines, see below), so there's no
 * board_hw_config_get()-style runtime choice to make here at all. */
#define BOARD_NUM_LINES 2

/* ---- I2S (WM8731 codec, ESP32 is master) ---- */
#define BOARD_I2S_MCLK    GPIO_NUM_0   /* XTI/MCLK  -> codec pin 25 */
#define BOARD_I2S_BCLK    GPIO_NUM_4   /* BCLK      -> codec pin 3  */
#define BOARD_I2S_LRCK    GPIO_NUM_5   /* DACLRC/ADCLRC (tied)      */
#define BOARD_I2S_DOUT    GPIO_NUM_6   /* MCU -> DACDAT (codec pin 4, playback) */
#define BOARD_I2S_DIN     GPIO_NUM_7   /* ADCDAT -> MCU (codec pin 6, record)   */

/* ---- I2C (WM8731 control) ---- */
#define BOARD_I2C_SDA     GPIO_NUM_22
#define BOARD_I2C_SCL     GPIO_NUM_23
#define BOARD_WM8731_ADDR 0x1A         /* MODE=GND, CSB=GND */
#define BOARD_CODEC_I2C_ADDR BOARD_WM8731_ADDR

/* ---- AG1170 SLIC control, per line ----
 * SHK : SLIC -> MCU (input)  1 = off-hook (after level conditioning)
 * F/R : MCU  -> SLIC (out)   toggled 20-25 Hz to ring; static otherwise
 * RM  : MCU  -> SLIC (out)   1 only during ringing
 * PD  : MCU  -> SLIC (out)   open-collector; see BOARD_PD_LEVEL_RUN below
 */
#define BOARD_LINE0_SHK   GPIO_NUM_1
#define BOARD_LINE0_FR    GPIO_NUM_2
#define BOARD_LINE0_RM    GPIO_NUM_3
#define BOARD_LINE0_PD    GPIO_NUM_14

#define BOARD_LINE1_SHK   GPIO_NUM_19
#define BOARD_LINE1_FR    GPIO_NUM_21
#define BOARD_LINE1_RM    GPIO_NUM_20
#define BOARD_LINE1_PD    GPIO_NUM_18

/* This PCB has no microSD socket at all (unlike SMD2, where it's an
 * alternate use of line 2's GPIO pads) -- board_hw_config_get() (board.h)
 * always reports has_microsd=false here, so sdcard_init() returns early
 * before ever touching these. Placeholders only exist so sdcard.c, which
 * now always compiles its real implementation (board line count/microSD
 * are runtime choices, not separate firmware builds), has something to
 * reference on this board type too. */
#define BOARD_SD_CS       GPIO_NUM_NC
#define BOARD_SD_SCLK     GPIO_NUM_NC
#define BOARD_SD_MOSI     GPIO_NUM_NC
#define BOARD_SD_MISO     GPIO_NUM_NC

/*
 * PD drive polarity.
 * The AG1170 PD pin must NEVER see a logic high directly; it is driven by an
 * open-collector transistor (BC846) on this board. Per the AG1170 figure:
 *   "High input for Power Down, Low input for free run".
 * The MCU GPIO drives the transistor base, so:
 *   GPIO LOW  -> transistor off -> PD open  -> SLIC RUNS
 *   GPIO HIGH -> transistor on  -> PD low   -> SLIC POWERED DOWN
 * If your transistor stage inverts this, flip these two macros.
 */
#define BOARD_PD_LEVEL_RUN        0
#define BOARD_PD_LEVEL_POWERDOWN  1

/* SHK active level (after conditioning): 1 = off-hook. */
#define BOARD_SHK_OFFHOOK_LEVEL   1

/* ---- Debug UART headers (informational; default console uses these) ---- */
#define BOARD_UART_TX     GPIO_NUM_16
#define BOARD_UART_RX     GPIO_NUM_17

/* Convenience accessors keyed by line index. */
typedef struct {
    gpio_num_t shk;
    gpio_num_t fr;
    gpio_num_t rm;
    gpio_num_t pd;
} board_line_pins_t;

static inline board_line_pins_t board_line_pins(int line)
{
    if (line == 0) {
        return (board_line_pins_t){ BOARD_LINE0_SHK, BOARD_LINE0_FR,
                                    BOARD_LINE0_RM,  BOARD_LINE0_PD };
    }
    return (board_line_pins_t){ BOARD_LINE1_SHK, BOARD_LINE1_FR,
                                BOARD_LINE1_RM,  BOARD_LINE1_PD };
}

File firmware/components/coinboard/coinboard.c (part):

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static void cap_summary(int line)
{
    static const int IN[4] = { COINBOARD_BIT_NICKEL, COINBOARD_BIT_DIME, COINBOARD_BIT_QUARTER, COINBOARD_BIT_COIN4 };
    static const char *const NAME[3] = { "nickel", "dime", "quarter" };
    static const char TAG4[4] = { 'N', 'D', 'Q', '4' };
    lock();
    int n = s_cap_n;
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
